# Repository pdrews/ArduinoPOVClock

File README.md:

# ArduinoPOVClock
Code and PCB Layout for POV clock based on 8-bit MCU programmed in Arduino

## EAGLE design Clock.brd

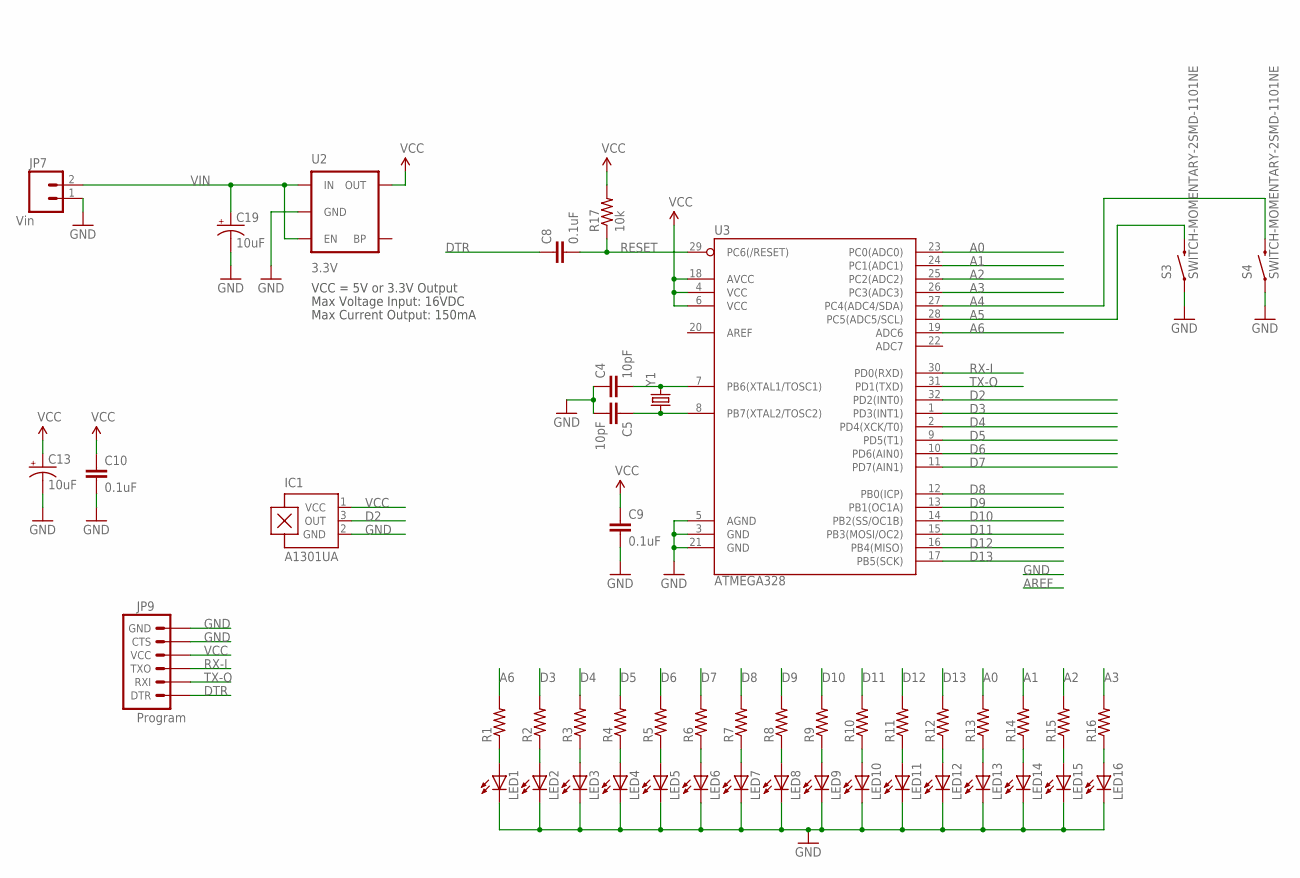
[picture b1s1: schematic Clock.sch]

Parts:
C4, C5: 10pF; 0603-CAP
C8, C9, C10: 0.1uF; 0603-CAP
C13, C19: 10uF; EIA3216
IC1: A1301UA; SIP3-UA
JP7: Vin; 1X02
JP9: Program; 1X06-SMD
LED1, LED2, LED3, LED4, LED5, LED6, LED7, LED8, LED9, LED10, LED11, LED12, LED13, LED14, LED15, LED16: LEDCHIPLED_1206; CHIPLED_1206
R1, R2, R3, R4, R5, R6, R7, R8, R9, R10, R11, R12, R13, R14, R15, R16: R-US_R0603; R0603
R17: 10k; 0603-RES
S3, S4: SWITCH-MOMENTARY-2SMD-1101NE; TACTILE-SWITCH-1101NE
U2: 3.3V; SOT23-5
U3: ATMEGA328; TQFP32-08
Y1: CRYSTAL5X3; CRYSTAL-SMD-5X3

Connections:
A0: R13.2, U3.23 (PC0(ADC0))
A1: R14.2, U3.24 (PC1(ADC1))
A2: R15.2, U3.25 (PC2(ADC2))
A3: R16.2, U3.26 (PC3(ADC3))
A4: S4.2, U3.27 (PC4(ADC4/SDA))
A5: S3.2, U3.28 (PC5(ADC5/SCL))
A6: R1.2, U3.19 (ADC6)
D2: IC1.3 (OUT), U3.32 (PD2(INT0))
D3: R2.2, U3.1 (PD3(INT1))
D4: R3.2, U3.2 (PD4(XCK/T0))
D5: R4.2, U3.9 (PD5(T1))
D6: R5.2, U3.10 (PD6(AIN0))
D7: R6.2, U3.11 (PD7(AIN1))
D8: R7.2, U3.12 (PB0(ICP))
D9: R8.2, U3.13 (PB1(OC1A))
D10: R9.2, U3.14 (PB2(SS/OC1B))
D11: R10.2, U3.15 (PB3(MOSI/OC2))
D12: R11.2, U3.16 (PB4(MISO))
D13: R12.2, U3.17 (PB5(SCK))
DTR: C8.1, JP9.1 (DTR)
GND: C4.1, C5.2, C9.2, C10.2, C13.C (-), C19.C (-), IC1.2 (GND), JP7.1, JP9.5 (CTS), JP9.6 (GND), LED1.C, LED2.C, LED3.C, LED4.C, LED5.C, LED6.C, LED7.C, LED8.C, LED9.C, LED10.C, LED11.C, LED12.C, LED13.C, LED14.C, LED15.C, LED16.C, S3.1, S4.1, U2.2 (GND), U3.3 (GND), U3.5 (AGND), U3.21 (GND)
unnamed: C4.2, U3.7 (PB6(XTAL1/TOSC1)), Y1.3 (2)
unnamed: LED1.A, R1.1
unnamed: C5.1, U3.8 (PB7(XTAL2/TOSC2)), Y1.1
unnamed: LED2.A, R2.1
unnamed: LED3.A, R3.1
unnamed: LED4.A, R4.1
unnamed: LED5.A, R5.1
unnamed: LED6.A, R6.1
unnamed: LED7.A, R7.1
unnamed: LED8.A, R8.1
unnamed: LED9.A, R9.1
unnamed: LED10.A, R10.1
unnamed: LED11.A, R11.1
unnamed: LED12.A, R12.1
unnamed: LED13.A, R13.1
unnamed: LED14.A, R14.1
unnamed: LED15.A, R15.1
unnamed: LED16.A, R16.1
RESET: C8.2, R17.1, U3.29 (PC6(/RESET))
RX-I: JP9.3 (TXO), U3.30 (PD0(RXD))
TX-O: JP9.2 (RXI), U3.31 (PD1(TXD))
VCC: C9.1, C10.1, C13.A (+), IC1.1 (VCC), JP9.4 (VCC), R17.2, U2.5 (OUT), U3.4 (VCC), U3.6 (VCC), U3.18 (AVCC)
VIN: C19.A (+), JP7.2, U2.1 (IN), U2.3 (EN)

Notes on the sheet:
VCC = 5V or 3.3V Output
Max Voltage Input: 16VDC
Max Current Output: 150mA

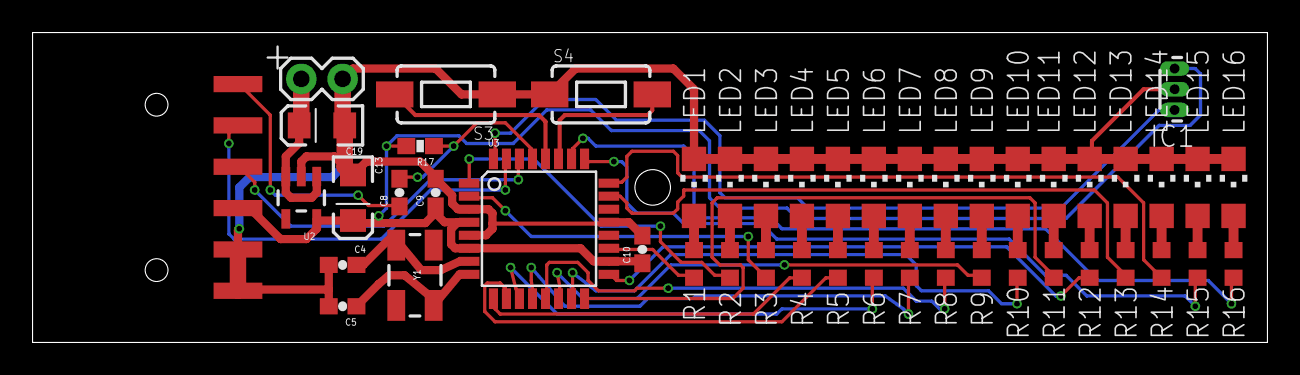
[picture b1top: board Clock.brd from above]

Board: 2 copper layers, 75.9 x 19.0 mm, 48 parts (0 on the bottom side), 44 nets.

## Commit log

2017-09-17 Initial code commit
2017-09-17 Moved arduino sketch into sketch folder
2017-09-17 Smiley face!!!
2017-09-28 Fully routed board
2017-09-28 Board updates for final board fab.
2017-10-28 Initial commit of holder plate
2017-12-01 Demo code to work with the newest clock version

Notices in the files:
parts and their libraries:
SparkFun-FreqCtrl: Licensing: Creative Commons ShareAlike 4.0 International - https://creativecommons.org/licenses/by-sa/4.0
